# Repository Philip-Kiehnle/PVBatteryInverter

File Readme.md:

# PVBatteryInverter - Highly Efficient Photovoltaic and Battery Hybrid Inverter using GaN Semiconductors
This project was inspired by multiple drivers:
 * AC-connected battery systems have disadvantages in terms of charging efficiency ( PV -> DC/AC -> AC/DC -> Battery ) and cost/environmental impact, because of the additional inverter.  
 A multilevel battery converter is efficient but does not offer a DC port for PV and thus, increases installed converter power in the grid and grid operators have to calculate the worst case for grid utilization.
 * DC-connected battery systems do not guarantee a better efficiency by default. E.g. in case of a large inverter (~10 kW) operating under small loads during nighttime (30–150 Watt).
 * Commercial solutions often require an additional power meter for the self-consumption power control. In my opinion, this is a complete waste of time, space, resources and energy:
   * The installation is complicated, and requires space in the meter cabinet.
   * The additional power meter requires extra power of 0.4–2 Watt.
   * The additional power meter has an offset from the official meter measurement, meaning it cannot be used for exact zero-import control.
   * The digital energy meters in Germany already offer an optical interface, which can be set to send the actual power every second  [More details below](#head_electricityMeter)
 * GaN instead of SiC or Si-IGBT offers improved efficiency.
 * No GaN-based inverter is out there at the moment (9.12.2023)
 * Second-life 6 kWh battery was available
 * GaN full-bridge cells were available from another project
 * New west oriented PV plant has some shaded areas, which are directly connected to microinverter. But 8 PV-modules are unshaded most of the time and require a string inverter. A Hybrid (PV+Battery) Inverter for the unshaded PV-modules and a microinverter for the shaded PV-modules looks like the optimal solution.

Let's build an efficient 2kW hybrid inverter, which solves all the problems shown above!

System Overview:

# Components

## PV Plant
```
8 x 405 W PV-modules in the string
STC:
Vmpp_module(25°C) = 36.48 V
Impp_module(25°C) = 11.10 A
Voc_module(25°C)  = 46.30 V

Temperature Coefficients of Voc = -0.28 %
Voc_module(-15°C)  = 51.49 V
Voc_string(-15°C)  = 411.9 V -> 650 V GaN semiconductors
```

## High-Voltage Battery
```
nunm_cells = 96
Vmin = 96 * 3.3 V = 316.8 V (grid feed-in is only possible when grid rms voltage is below 224 V or by using reactive power)
Vnom = 96 * 3.7 V = 355.2 V
Vmax = 96 * 4.2 V = 403.2 V
energy = 18 Ah * 355.2 V = 6.4 kWh
```

## Inverter Housing
An unused inverter housing was available, including passive components like boost inductors and an LCL-filter, which can be reused.

A control PCB and GaN Full-Bridge PCBs were added. This picture was taken during the development phase:

### PV input
Common-Mode-Choke (CMC) -> Capacitor: MKP 900V  12.5uF +-5% -> Inductor -> Diode for PV string protection during development -> GaN Half-Bridge

### LCL-Filter
Inverter side inductor: 1mH

### GaN Full-Bridge
```
GaN semiconductors:
Gan Systems GS66508B 650 V
Rds_on(25°C)  =  50 mOhm
Rds_on(112°C) = 100 mOhm

estimated loss:
I = 2000 W ÷ 230 V = 8.7 A
50 % conduction of low and high-side switch
Pcond(112°C) = 0.5*0.1 Ohm*(8.7 A)^2 = 3.8 W per switch

Switching loss (according to datasheet at Vds = 400 V, Ids = 15 A):
Eon=47.5 µJ
Eoff=8 µJ
Pswitch = 20 kHz * (47.5+8) µJ = 1.1 W
-> 4.9 W have to be dissipated for each transistor 

Thermal Model:
R_JC = 0.5 K/W (manufacturer)
R_PCB = 3.39 K/W
R_TIM = 0.28 K/W
R_HSA = 4.8 K/W
R= 8.97 K/W
Thermal interface material coefficient seems too optimistic -> use R=10K/W
With ambient 40°C and junction = 112°C each transistor can dissipate P=(112-40)/10=7.2W
This assumption has enough tolerance because:
  -operating junction temperature is 150°C and not 112°C
  -dissipated power will be lower than 7.2W

If the power rating is set to 2300 W, the loss will increase to:
Ploss = Pswitch + 0.5*0.1 Ohm*(10 A)^2 = 1.1 W + 5 W = 6.1 W
But the inverter's inductors had an original design power of 2 kW. On the other hand, the ripple is lower than in the original design, because of an increased switching frequency.
This increases the core loss but the central inductor of phase L2 can be assumed as a heat sink, because it is not used.

Start heatsink fan at 1200W (5.2A) assume 90mOhm:
Ploss = Pswitch + 0.5*0.09 Ohm*(5.2 A)^2 = 1.1 W + 1.2 W = 2.3 W
Minimum runtime is 30 sec, stop if power after timer runtime is lower than 1 kW. Restart timer if power > 1.2 kW during fan runtime.
```

### Control board [PVBatteryInverter_Mainboard](PVBatteryInverter_Mainboard)
An STM32G474 microcontroller is used to control the system.

#### Code Execution:

HRTIM 20 kHz controls Grid Full-Bridge
1. HRTIM period triggers ADC1
2. ADC1 DMA done calls ADC_ConvComplete with hadc1 instance
3. ADC2 for PV current is started (two ADCs simultaneously cause disturbance!)
4. AC control algorithm is executed and new dutycycle is set
5. 45 µs after ADC2 start, the 128 PV/DC current samples are acquired and ADC DMA calls ADC_ConvComplete with hadc2 instance
6. DC control algorithm is executed and new dutycycle is set. Exact timing not relevant for slow MPP-Tracker
7. wait for new ADC1 samples

## Energy Management System
Todo: opensource the git repo and add link

## Default Electricity Meter

The Iskra electricity meter offers a power resolution of 1 Watt and a temporal resolution of 1 second.  
Its permanent energy counting registers are written every 100 mWh.  
This equals to a power mismatch of 360 W for 1 second.  
So the controller has to avoid that, which is possible most of the time.  
In case of large load steps, like hobs switching with 2 kW, there will be a mismatch.  
But experiments have shown that for a cooking session of 30 minutes, a mismatch of about 12 Wh occurs.  
If this amount is equally spread over 24 hours, the mismatch in each hour is 0.5 W.
To beat that value, an additional energy meter must:
  * consume less than 0.5 W
  * offer better temporal resolution than 1 second
  * offer no offset compared to the main electricity meter, or use an offset in feed-in direction and thus always feeds a little bit of power into the grid
  * come at no cost

This demonstrates the whole extent of stupidity to install an additional energy meter, if a digital electricity meter is already installed!  
A detailed analysis is also carried out in the [PowerSensorEmulator
](https://github.com/Philip-Kiehnle/PowerSensorEmulator
) repository.

# Efficiency

## Power Consumption
Assuming 90 % efficiency of the 5 V power supply.

### Mode "Connected to AC Grid - Passive"
The gate signals are turned off whenever there is no exchange of AC power.

BMS: 6 W  
Smartphone: 1 W  
PV-Boost GaN Full-Bridge not switching: 5 V ⋅ 90 mA / 0.9 = 0.5 W  
Grid GaN Full-Bridge not switching: 5 V ⋅ 90 mA / 0.9 = 0.5 W  
Grid Relay: 0.4 W  
STM32_PVBatteryInverter PCB:  5 V ⋅ 50 mA / 0.9 = 0.28 W (todo: check)  
STM32_BatterySupervisor PCB:  5 V ⋅ 40 mA / 0.9 = 0.22 W (todo: check)  

**Total: 8.9 W**

### Mode "Idle"
BMS 12 V power supply is OFF, so the idle consumption is reduced to **2.9 W**.  
The BMS reactivation and the routine for closing contactors takes about 10 seconds.

### Mode "Connected to AC Grid - Active"
Todo: measure efficiency curve

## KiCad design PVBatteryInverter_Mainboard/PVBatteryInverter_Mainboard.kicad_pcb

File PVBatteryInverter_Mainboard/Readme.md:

# Aisler PCB made in Germany
minium amount: 3pcs  
area: 100mm*60mm = 60cm²  
```
Price Budget 2-Layer: 10€ + 3* 60*0.0525€/cm² = 19,45€ -> 23,15€
Price HD 2-Layer:     12€ + 3* 60*0.084€/cm²  = 27,12€ -> 32,27€
Price HD 4-Layer:     12€ + 3* 60*0.117€/cm²  = 33,06€ -> 39,34€
```

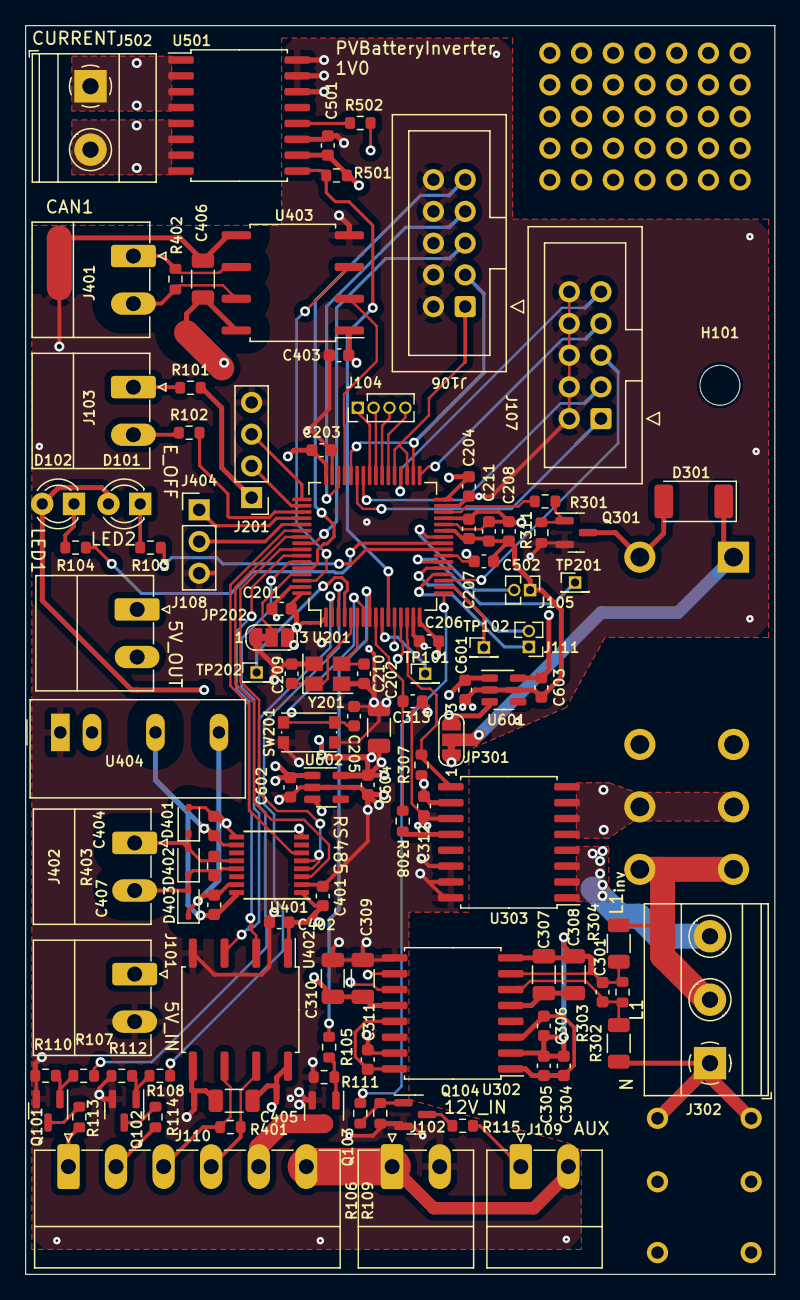
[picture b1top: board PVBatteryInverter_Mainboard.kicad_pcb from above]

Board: 4 copper layers, 60.0 x 100.0 mm, 116 parts (1 on the bottom side), 100 nets.

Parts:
C201, C203, C204, C205, C206, C211, C306, C311, C312, C401, C402, C403, C404, C407, C501: 100n; C_0603_1608Metric
C202: 4u7; C_1206_3216Metric
C207: 10n; C_0603_1608Metric
C208, C304: 1u; C_0603_1608Metric
C209, C210, C301: 10p; C_0603_1608Metric
C305: 1n; C_0603_1608Metric
C307, C405, C406: 100n; C_1206_3216Metric
C308, C309: 1n; C_1206_3216Metric
C310: 1µ; C_1206_3216Metric
C313, C502: 2n2; C_0603_1608Metric
C601, C602, C603, C604: 1µ; C_0603_1608Metric
D101, D102: LED; LED_D3.0mm
D301: US1D 200V 1A 50ns Silizium SMA; D_MELF
D401, D402, D403: D_TVS; D_SOD-323
H101: MountingHole; MountingHole_3.2mm_M3
J101: 5V_IN; PhoenixContact_MC_1,5_2-G-3.81_1x02_P3.81mm_Horizontal
J102: 12V_IN; PhoenixContact_MC_1,5_2-G-3.81_1x02_P3.81mm_Horizontal
J103: EMERGENY_OFF; PhoenixContact_MC_1,5_2-G-3.81_1x02_P3.81mm_Horizontal
J104: TIM; PinHeader_1x04_P1.27mm_Vertical
J105: ADC2_12; PinHeader_1x02_P1.27mm_Vertical
J106: FB_Boost; IDC-Header_2x05_P2.54mm_Vertical
J107: FB_Grid; IDC-Header_2x05_P2.54mm_Vertical
J108: 5V_OUT; PhoenixContact_MC_1,5_2-G-3.81_1x02_P3.81mm_Horizontal
J109: AUX_OpenDrain; PhoenixContact_MC_1,5_2-G-3.81_1x02_P3.81mm_Horizontal
J110: BMS; PhoenixContact_MC_1,5_6-G-3.81_1x06_P3.81mm_Horizontal
J111: ADC2_3-4; PinHeader_1x02_P1.27mm_Vertical
J201: SW_DBG; PinHeader_1x04_P2.54mm_Vertical
J302: 230V; TerminalBlock_Phoenix_MKDS-1,5-3-5.08_1x03_P5.08mm_Horizont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
J401: CAN1; PhoenixContact_MC_1,5_2-G-3.81_1x02_P3.81mm_Horizontal
J402: RS485; PhoenixContact_MC_1,5_2-G-3.81_1x02_P3.81mm_Horizontal
J404: UART; PinHeader_1x03_P2.54mm_Vertical
J502: Current sense; TerminalBlock_Phoenix_MKDS-1,5-2-5.08_1x02_P5.08mm_Horizont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
JP202: BOOT_MODE; SolderJumper-3_P1.3mm_Bridged12_RoundedPad1.0x1.5mm_NumberL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
JP301: SolderJumper_3_Bridged12; SolderJumper-3_P1.3mm_Bridged12_RoundedPad1.0x1.5mm_NumberL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
NT301, NT403, NT404: NetTie_2; NetTie-2_SMD_Pad0.5mm
NT401, NT402: NetTie_2; NetTie-2_SMD_Pad2.0mm
NT601: GNDA; NetTie-2_SMD_Pad0.5mm
Q101, Q102, Q104: BSS138; SOT-23
Q103, Q301: IRLML2502; SOT-23
R101, R102: 1k; R_0603_1608Metric
R103, R104, R308, R502: 220; R_0603_1608Metric
R105, R106, R107, R108, R113, R114, R115, R301: 100; R_0603_1608Metric
R109, R110, R111, R112, R311: 100k; R_0603_1608Metric
R302, R304: 470k; R_1206_3216Metric
R303: 2.70k; R_0603_1608Metric
R307, R501: 10k; R_0603_1608Metric
R401, R402, R403: 120; R_0603_1608Metric
RL301: JW2; Relay_DPDT_Panasonic_JW2
SW201: RESET; SW_Push_1P1T_NO_CK_KMR2
TP101: ADC1_IN8; PinHeader_1x01_P1.27mm_Vertical
TP102: TIM3_CH2; PinHeader_1x01_P1.27mm_Vertical
TP201: PC4; PinHeader_1x01_P1.27mm_Vertical
TP202: PC15; PinHeader_1x01_P1.27mm_Vertical
U201: STM32G474RETx; LQFP-64_10x10mm_P0.5mm
U302: AMC3330; SOIC-16W_7.5x10.3mm_P1.27mm
U303, U501: MCA1101-50-5; SOIC-16W_7.5x10.3mm_P1.27mm
U401: ISO1500; SSOP-16_3.9x4.9mm_P0.635mm
U402, U403: ISO1050DUB; SOP-8_6.62x9.15mm_P2.54mm
U404: TMR_1-0511; Converter_DCDC_TRACO_TMR-1-xxxx_Single_THT
U601, U602: TPS7A0333PDBVR; SOT-23-5
Y201: 12 MHz; Crystal_SMD_SeikoEpson_TSX3225-4Pin_3.2x2.5mm

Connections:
+3V3: C201.1, C202.1, C203.1, C204.1, C206.1, C309.1, C310.1, C401.1, C402.1, C403.1, C604.1, D101.2 (A), D102.2 (A), J201.1, JP202.3 (B), R101.2, U201.1 (VBAT), U201.16 (VDD), U201.32 (VDD), U201.48 (VDD), U201.64 (VDD), U302.12 (VDD), U401.1 (VCC1), U402.1 (VCC1), U403.1 (VCC1), U602.5 (OUT)
+5V: C312.1, C501.1, C601.1, C602.1, J101.1, J108.1, J108.2, JP301.3 (B), NT401.1, NT403.1, R307.2, R501.2, U303.10 (VCC), U404.2 (+VIN), U501.10 (VCC), U601.1 (IN), U601.3 (EN), U602.1 (IN), U602.3 (EN)
+12V: J102.1, J109.2, J110.6, JP301.1 (A)
/AC grid/AMC3330_OUTN: U201.13 (PA1), U302.10 (OUTN)
/AC grid/AMC3330_OUTP: U201.12 (PA0), U302.11 (OUTP)
/AC grid/Contactor_{Grid}: R301.1, U201.30 (PB10)
/AC grid/Igrid_{+}: C313.1, R308.2, U201.9 (PC1)
/AC grid/L1_{grid_sw}: RL301.3, RL301.6, U303.5 (IP-), U303.6 (IP-), U303.7 (IP-), U303.8 (IP-)
/AC grid/L1_{grid}: J302.2, R304.2, RL301.4, RL301.5
/AC grid/L1_{inverter}: J302.3, U303.1 (IP+), U303.2 (IP+), U303.3 (IP+), U303.4 (IP+)
/AC grid/N: J302.1, R302.1
/AC grid/nFAULT_{MCA1101}: R307.1, U201.14 (PA2), U303.9 (~FAULTB)
/BMS_GND: J110.5, Q103.3 (D)
/Communication/5V_CAN1: C406.1, NT401.2, U403.8 (VCC2)
/Communication/5V_CAN2: C405.1, NT403.2, U402.8 (VCC2)
/Communication/5V_RS485: C404.1, C407.1, U401.10 (VCC2), U401.16 (VCC2), U404.4 (+VOUT)
/Communication/CAN1_{RX}: U201.45 (PA11), U403.2 (RXD)
/Communication/CAN1_{TX}: U201.62 (PB9), U403.3 (TXD)
/Communication/CAN2_{RX}: U201.58 (PB5), U402.2 (RXD)
/Communication/CAN2_{TX}: U201.59 (PB6), U402.3 (TXD)
/Communication/GND_CAN1: C406.2, NT402.2, U403.5 (GND2)
/Communication/GND_CAN2: C405.2, NT404.2, U402.5 (GND2)
/Communication/GND_RS485: C404.2, C407.2, D401.2 (A2), D403.1 (A1), U401.9 (GND2), U401.15 (GND2), U404.6 (-VOUT)
/Communication/RS485_{EN}: U201.57 (PB4), U401.4 (~RE), U401.5 (DE)
/Communication/RS485_{RX}: U201.55 (PD2), U401.3 (R)
/Communication/RS485_{TX}: U201.54 (PC12), U401.6 (D)
/Communication/UART_{RX}: J404.2, U201.53 (PC11)
/Communication/UART_{TX}: J404.1, U201.52 (PC10)
/Cont_{Bat2DCboost}: J110.1, R113.2
/DCcurrent_sense/CS+: J502.1, U501.1 (IP+), U501.2 (IP+), U501.3 (IP+), U501.4 (IP+)
/DCcurrent_sense/CS-: J502.2, U501.5 (IP-), U501.6 (IP-), U501.7 (IP-), U501.8 (IP-)
/DCcurrent_sense/Ipv_{+}: C502.1, R502.2, U201.23 (PC5)
/DCcurrent_sense/nFAULT_{MCA1101}: R501.1, U201.11 (PC3), U501.9 (~FAULTB)
/Microcontroller/+3V3A_{MCU}: C207.1, C208.1, C211.1, C603.1, U201.28 (VREF+), U201.29 (VDDA), U601.5 (OUT)
/Microcontroller/ADC1_IN8: TP101.1, U201.10 (PC2)
/Microcontroller/ADC2_IN3: J111.1, U201.20 (PA6)
/Microcontroller/ADC2_IN4: J111.2, U201.21 (PA7)
/Microcontroller/ADC2_IN12: J105.2, U201.26 (PB2)
/Microcontroller/BOOT0: JP202.2 (C), U201.61 (PB8)
/Microcontroller/EmergencyOFF: R102.2, U201.51 (PA15)
/Microcontroller/FB_Boost_{EN}: J106.9, U201.60 (PB7)
/Microcontroller/FB_Boost_{OverTemp}: J106.7, U201.46 (PA12)
/Microcontroller/FB_Boost_{PWMA}: J106.3, U201.34 (PB12), U201.44 (PA10)
/Microcontroller/FB_Boost_{PWMB}: J106.1, U201.35 (PB13), U201.37 (PB15)
/Microcontroller/FB_Boost_{VdcData}: J106.5, U201.56 (PB3)
/Microcontroller/FB_Grid_{EN}: J107.9, U201.36 (PB14)
/Microcontroller/FB_Grid_{OverTemp}: J107.7, U201.33 (PB11)
/Microcontroller/FB_Grid_{PWMA}: J107.3, U201.42 (PA8)
/Microcontroller/FB_Grid_{PWMB}: J107.1, U201.43 (PA9)
/Microcontroller/FB_Grid_{VdcData}: J107.5, U201.19 (PA5)
/Microcontroller/HRTIM1CH_{E1}: J104.2, U201.40 (PC8)
/Microcontroller/HRTIM1CH_{E2}: J104.1, U201.41 (PC9)
/Microcontroller/HRTIM1CH_{F1}: J104.4, U201.38 (PC6)
/Microcontroller/HRTIM1CH_{F2}: J104.3, U201.39 (PC7)
/Microcontroller/LED1: R103.1, U201.24 (PB0)
/Microcontroller/LED2: R104.1, U201.25 (PB1)
/Microcontroller/NRST: C205.1, SW201.1 (A), U201.7 (PG10)
/Microcontroller/PF0: C209.2, U201.5 (PF0), Y201.1
/Microcontroller/PF1: C210.2, U201.6 (PF1), Y201.3
/Microcontroller/SWCLK: J201.2, U201.50 (PA14)
/Microcontroller/SWDIO: J201.3, U201.49 (PA13)
/Microcontroller/TIM3_CH2: TP102.1, U201.18 (PA4)
Aux_OpenDrain: R106.1, U201.17 (PA3)
BMS_Power: R105.1, U201.8 (PC0)
CAN2_{H}: J110.4, R401.1, U402.7 (CANH)
CAN2_{L}: J110.3, R401.2, U402.6 (CANL)
Contactor_{Bat2DCboost}: R107.1, U201.2 (PC13)
Contactor_{Bat2Inverter}: R108.1, U201.3 (PC14)
GND: C201.2, C202.2, C203.2, C204.2, C205.2, C206.2, C209.1, C210.1, C309.2, C310.2, C311.2, C312.2, C313.2, C401.2, C402.2, C403.2, C501.2, C601.2, C602.2, C604.2, J101.2, J102.2, J106.2, J106.4, J106.6, J106.8, J106.10, J107.2, J107.4, J107.6, J107.8, J107.10, J201.4, J404.3, JP202.1 (A), NT402.1, NT404.1, NT601.2, Q101.2 (S), Q102.2 (S), Q103.2 (S), Q104.2 (S), Q301.2 (S), R109.1, R110.1, R111.1, R112.1, R311.1, SW201.2 (B), U201.15 (VSS), U201.31 (VSS), U201.47 (VSS), U201.63 (VSS), U302.9 (GND), U302.15 (DCDC_GND), U303.11 (GND), U303.14 (GND2), U303.15 (GND), U303.16 (VOC), U401.2 (GND1), U401.8 (GND1), U402.4 (GND1), U403.4 (GND1), U404.1 (-VIN), U501.11 (GND), U501.14 (GND2), U501.15 (GND), U501.16 (VOC), U601.2 (GND), U602.2 (GND), Y201.2, Y201.4
GNDA: C207.2, C208.2, C211.2, C502.2, C603.2, J105.1, NT601.1, U201.27 (VSSA)
unnamed: D101.1 (K), R103.2
unnamed: D102.1 (K), R104.2
unnamed: D301.2 (A), Q301.3 (D), RL301.8
unnamed: D301.1 (K), JP301.2 (C), RL301.1
unnamed: D401.1 (A1), D402.2 (A2), J402.1, R403.1, U401.12 (A)
unnamed: D402.1 (A1), D403.2 (A2), J402.2, R403.2, U401.13 (B)
unnamed: J103.1, R101.1
unnamed: J103.2, R102.1
unnamed: J109.1, R115.2
unnamed: J110.2, R114.2
unnamed: J401.1, R402.1, U403.6 (CANL)
unnamed: J401.2, R402.2, U403.7 (CANH)
unnamed: Q101.3 (D), R113.1
unnamed: Q101.1 (G), R107.2, R110.2
unnamed: Q102.3 (D), R114.1
unnamed: Q102.1 (G), R108.2, R112.2
unnamed: Q103.1 (G), R105.2, R111.2
unnamed: Q104.3 (D), R115.1
unnamed: Q104.1 (G), R106.2, R109.2
unnamed: Q301.1 (G), R301.2, R311.2
unnamed: TP201.1, U201.22 (PC4)
unnamed: TP202.1, U201.4 (PC15)
unnamed: C304.2, C305.2, C306.1, C307.2, C308.2, NT301.2, U302.2 (DCDC_HGND), U302.8 (HGND)
unnamed: C311.1, U302.13 (LDO_OUT), U302.16 (DCDC_IN)
unnamed: C304.1, C305.1, C306.2, U302.1 (DCDC_OUT), U302.3 (HLDO_IN)
unnamed: C307.1, C308.1, U302.5 (HLDO_OUT)
unnamed: C301.2, NT301.1, R303.2, R304.1, U302.7 (INN)
unnamed: C301.1, R302.2, R303.1, U302.6 (INP)
unnamed: R308.1, U303.12 (Vout)
unnamed: R502.1, U501.12 (Vout)

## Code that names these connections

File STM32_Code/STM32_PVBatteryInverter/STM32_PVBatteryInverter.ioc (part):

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Mcu.Name=STM32G474R(B-C-E)Tx
Mcu.Package=LQFP64
Mcu.UserName=STM32G474RETx
PA0.Mode=IN1-Differential
PA0.Signal=ADC1_IN1
PA1.Mode=IN1-Differential
PA1.Signal=ADC1_IN2
PA10.Signal=S_TIM1_CH3
PA11.Signal=FDCAN1_RX
PA12.GPIOParameters=GPIO_PuPd,GPIO_ModeDefaultEXTI
PA12.GPIO_ModeDefaultEXTI=GPIO_MODE_IT_RISING
PA12.GPIO_PuPd=GPIO_PULLUP
PA12.Signal=GPXTI12
PA13.Mode=Serial_Wire
PA13.Signal=SYS_JTMS-SWDIO
PA14.Mode=Serial_Wire
PA14.Signal=SYS_JTCK-SWCLK
PA15.GPIOParameters=GPIO_PuPd
PA15.GPIO_PuPd=GPIO_PULLDOWN
PA15.Signal=GPIO_Input
PA2.GPIOParameters=GPIO_ModeDefaultEXTI
PA2.GPIO_ModeDefaultEXTI=GPIO_MODE_IT_FALLING
PA2.Signal=GPXTI2
PA3.Signal=GPIO_Output
PA4.Signal=S_TIM3_CH2
PA5.Signal=S_TIM2_ETR
PA6.Signal=ADC2_IN3
PA7.Mode=INP
PA7.Signal=COMP2_INP
PA8.Mode=Output_TA1TA2
PA8.Signal=HRTIM1_CHA1
PA9.Mode=Output_TA1TA2
PA9.Signal=HRTIM1_CHA2
PB0.Signal=GPIO_Output
PB1.Signal=GPIO_Output
PB10.Signal=GPIO_Output
PB11.GPIOParameters=GPIO_PuPd,GPIO_ModeDefaultEXTI
PB11.GPIO_ModeDefaultEXTI=GPIO_MODE_IT_RISING
PB11.GPIO_PuPd=GPIO_PULLUP
PB11.Signal=GPXTI11
PB13.Mode=PWM Generation1 CH1N
PB13.Signal=TIM1_CH1N
PB14.Signal=GPIO_Output
PB15.Signal=TIM1_CH3N
PB2.Signal=ADC2_IN12
PB3.Signal=S_TIM4_ETR
PB4.Mode=Hardware Flow Control (RS485)
PB4.Signal=UART5_DE
PB5.Mode=FDCAN_Activate
PB5.Signal=FDCAN2_RX
PB6.Mode=FDCAN_Activate
PB6.Signal=FDCAN2_TX
PB7.Signal=GPIO_Output
PB9.Signal=FDCAN1_TX
PC0.Signal=GPIO_Output
PC1.Mode=IN7-Single-Ended
PC1.Signal=ADC1_IN7
PC10.Mode=Asynchronous
PC10.Signal=USART3_TX
PC11.Mode=Asynchronous
PC11.Signal=USART3_RX
PC12.Mode=Asynchronous
PC12.Signal=UART5_TX
PC13.Signal=GPIO_Output
PC14-OSC32_IN.Signal=GPIO_Output
PC15-OSC32_OUT.Signal=GPIO_Output
PC3.GPIOParameters=GPIO_ModeDefaultEXTI
PC3.GPIO_ModeDefaultEXTI=GPIO_MODE_IT_FALLING
PC3.Signal=GPXTI3
PC4.Signal=GPIO_Output
PC5.Mode=IN11-Single-Ended
PC5.Signal=ADC2_IN11
PC6.Signal=HRTIM1_CHF1
PC7.Signal=HRTIM1_CHF2
PC8.Signal=HRTIM1_CHE1
PC9.Signal=HRTIM1_CHE2
PD2.Mode=Asynchronous
PD2.Signal=UART5_RX
PF0-OSC_IN.Mode=HSE-External-Oscillator
PF0-OSC_IN.Signal=RCC_OSC_IN
PF1-OSC_OUT.Mode=HSE-External-Oscillator
PF1-OSC_OUT.Signal=RCC_OSC_OUT
RCC.HSE_VALUE=12000000
RCC.SYSCLKFreq_VALUE=170000000
RCC.SYSCLKSource=RCC_SYSCLKSOURCE_PLLCLK
board=custom

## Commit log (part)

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2023-12-09 PCB production V1; pin planning complete
2023-12-26 fixed some PCB components and added notes in schematic for PCB V2
2023-12-26 tested CAN, PWM, UART, ADCs and all Sensors
2023-12-30 MPP Tracker tested with 19V supply 35W bulb as pre resistor; 32Ohm load resistor; 33kOhm Vdc sense
2024-01-05 tested AC control with 15V transformer, LCL filter and 4 Ohm series resistor; charging to 30Vdc successful
2024-01-07 implemented battery CAN bus commands
2024-01-19 MPP-Tracker in C++
2024-01-22 added watchdog; PV2AC with 10Watt at 48V
2024-01-22 without 5R6 AC precharge resistor; AC current 61mA offset; power consumption from DC and AC!
2024-01-26 PV boost auto switch to interleaved mode
2024-01-28 calib Vac and Vdc; implemented sml read -> tested in parallel with BMS and inverterdata output on same RS485 bus
2024-01-30 improved writing to monitor vars; grid voltage filter for matching amplitude; NO contactor or current feedforward
2024-01-30 monitor stream sync; MPPT too fast for grid control
2024-02-05 improved Vdc control speed; improved model, still mismatch: Pac=80W with 135W request
2024-02-07 fixed RC-lowpass freq
2024-02-17 inductor saturation LUT; dummy electr. meter
2024-03-16 PV battery charging and switch to PCC compensation tested
2024-03-17 improved battery_connected detection
2024-03-17 bootloader working; no autostart
2024-03-21 bootloader autostarts application if emergency button released at reset; RS485 update working
2024-03-21 battery update request always triggers send_inverterdata
2024-03-28 improved PV2AC mode; high PV input increases V_dc within seconds until EC_V_DC_SENSOR_FB_BOOST -> 4.0Aamp AC limit is not enough
2024-03-31 bootloader RS485 init after Jump, otherwise Comm in App broken; reworked hybrid states
2024-04-01 improved stability; optional print
2024-04-02 fixed mon_duty; fixed P_bat_const control; fixed AC turnoff during sunrise
2024-04-08 enabled global MPPT
2024-04-08 fixed gatedriver still disabled in PV2AC mode
2024-04-15 prevent short AC turnoff in the evening; improved battery handling and GMPPT
2024-04-16 status for enable_battery command
2024-04-23 added RS485 command interface
2024-05-02 fixed overvoltage error in transition from PV2AC to Hybrid mode
2024-05-03 added errorcodes for battery; fixed unaligned access in sml_parser
2024-05-13 reset microcontroller if battery switched off
2024-06-25 decreased PV start voltage; increased interval for RMS current fault
2024-10-10 charge Vcell to 3.50V instead of 3.56V added dynamic shift to direct voltage feedforward added grid voltage and freq error codes added external Pac control fixed power direction: grid to battery
2024-11-24 updated BMS struct (Kalman SoC and cycle counter)
2024-12-01 fixed battery_almost_full condition
2024-12-09 switched RS485 text parameter interface to Modbus; reset hybrid mode if main mode is changed
2024-12-14 reset Modbus after SML cycle (each second); update BMS lib
2024-12-16 shutdown of already discharged battery when PV power is low
2024-12-25 increased minimum battery cell voltage and prevent early battery shutdown to prevent BMS DEVICE_XREADY fault
2024-12-25 Battery Supervisor Board: CAN Bus RX test
2024-12-25 HV Vbat measurement circuit for PE connected microcontroller
2024-12-25 switched bootloader to internal oscillator
2024-12-30 STW_mBMS CAN read data and write balancing command
2025-01-02 fixed battery config; increased switching frequency to 40kHz, control still at 20kHz; tested voltage sensors and overcurrent Analog ADC watchdog
2025-01-07 5 minute charging test passed, using isolated AC-rectifier + 2x75W lightbulb as PV emulator; Test end with BMS unplug causing watchdog reset
2025-01-11 Battery_Supervisor: fixed voltage measurement circuit
2025-01-11 5 minute charging test passed using both PCBs; added shared code folder
2025-01-12 transmit battery current from Supervisor to Inverter
2025-01-13 Added GPIO interrupts for current sensor fault signals. Tested with Supervisor PCB and 60A AC pulse. Added GPIO interrupts for overtemperature. Tested with 1kOhm instead of NTC.
2025-01-13 Fixed overtemperature signal with 10nF. Added Kalman filter for SoC. Tested modbus registers for cell voltages. 15min 31W charging test passed.
2025-01-16 test with 320V DC and 33V AC RMS passed
2025-01-17 added 5V supply undervoltage detection to protect GaN from low gatevoltage. Tested trigger at ~4.65V.
2025-01-17 added nonlinear inductor model which was used in 48V system; remanent model is in rp-tfm repo
2025-01-19 new modbus regs: balancing state; v_pv reference
2025-01-19 31Vac 3.1Arms current test; 320Vdc
2025-01-26 230V AC grid with 30mA RCD and 2x1kW debug resistance: idle power ~3W, 15VA; disabled energy packet controller; avoid frequent contactor actions in case of grid voltage drop during contactor close; s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
2025-01-30 tested direct 230V AC grid with 30mA RCD; power meter: 2.6-5.2W, 80VA
2025-01-30 tested direct 230V AC grid with 10mA RCD
2025-01-30 added fan control
2025-01-31 improved UART monitoring
2025-02-01 ISR reordered to avoid noise of ADC2 disturbing ADC1; only one ADC should run at the same time; added second ISR debug pin; 8x oversampling for ADC1
2025-02-02 enabled and tested analog watchdog for AC current
2025-02-02 calib i_ac offset
2025-02-02 trigger ADC before CNT_MAX; checked ac duty calc duration max 5.1+18.4 = 23.5us < 25us
2025-02-03 fixed PI controller saturation behaviour; calib Vac offset with 325V sine; tuned PLL phase shift
2025-02-08 garage charging test with PV emulator 2x75W
2025-02-09 fixed sporadically read of 4 cell voltages as 0V
2025-02-09 fixed sporadically read of temperatures as 0; fixed battery current limit; increased AC power to 460W
2025-02-16 added battery PCB temperature; improved AC charging; adjusted battery temperature limits
2025-02-16 fixed external power immediate reset to 0; fixed PI-controller saturation
2025-02-17 improved AC charging; increased AC current; scaled p_ac; increased min cell voltage; decreased cell imbalance limit; use modbus SoC limits
2025-02-22 increased Vdc limit; increased Vcell max; set Kalman SoC estimation parameters in application
2025-02-23 BMS improvements; changed default PV boost stage, because stage 1 needs repair; turnoff AC if Vbat < Vgrid"
2025-02-24 prevent boost stage non sensed overcurrent due to high PV boost ratio or rapid change
2025-03-03 prevent bms power turnon without sufficient v_dc; BMS lib: improved CAN rx using multiple filters
2025-03-09 battery supervisor: improved CAN robustness; green LED shows contactor status
2025-03-10 reduced max battery temperature limit; error turns BMS 12V off; added p_ac controller; reduced limit for interleaved DCDC mode
2025-03-15 inline gate EN and contactor functions for faster response; added modbus commands
2025-03-15 added modbus p_bat_dischg_max
2025-03-16 increased AC current and error limit; increased min PV power; fixed BMS turnoff
2025-03-21 fixed PV low power cnt
2025-03-25 modbus reg for AC low power packet mode
2025-03-25 increased minimum cell voltage to avoid imbalance; increased AC power
2025-03-31 improved modbus write register (clamp before write); increased default minimum SoC
2025-04-12 increased AC power; battery i_discharge_max = 6A
2025-04-30 increased AC power to 1.5kW; increased BatterySupervisor pulse current limit from 10A to 15A; use advanced battery model for SoC estimation
2025-04-30 improved battery model: lower resistance; higher weight for coulomb counting
2025-05-13 increased AC power; added Modbus p_pcc_ref; added bat current limits for fault condition
2025-05-18 increased AC current error condition
2025-05-25 improved behaviour with empty battery; lowered max cell temp limit
2025-08-02 allow error reset after 30 seconds; improved PV2AC state switch; increased Pac and Iac_pulse_max; new MPPT: v_pv instead of dutycycle
2025-09-21 todo: cleanup readme
2025-10-08 increased Vpv,min; added SML submodule; increased controller speed for Ppcc controller
2025-11-22 fixed v_pv calculation; use PV2AC mode in the morning if p_pcc > 20W
2025-11-22 use PV2AC mode to start when V_pv > V_bat
2025-11-23 improved PV2AC and HYBRID mode change
2025-11-29 pv_power: calc RC lowpass; compensate DC link capacitor
2025-11-30 fixed mode change; pv_power: calc RC lowpass; compensate DC link capacitor
2025-12-15 added mode transition PV2AC to OFF in case of empty battery; improved PV2AC mode change; fixed voltage deviation error during battery turnoff
2026-02-28 reduced AC power to 1kW, which minimized AC current errors; started in december 2025, used until 28.2.2026
2026-03-02 added monitor variable ctrl_mode_AC; increased AC current
2026-03-04 modbus reg to disable use of battery; respect modbus SoC limit; limit MPPT power if required
2026-03-04 increased max Vdc
2026-05-17 interleaved MPPT
2026-05-18 added manual sensor calibration mode and PWM test mode
2026-05-21 use excess PV power for battery charging and ignore EMS charging power limit
2026-05-22 single boost converter stage
2026-06-04 added boost converter test
2026-06-05 improved dc_control
2026-06-13 preserve WatchdogRST flag in bootloader; check ISR runtime; check GaN reverse conduction (prevent system operation without active boost converter in case of high PV input current, which could damage 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
2026-06-29 increased max voltage and current
2026-06-30 fixed AC gatedriver pulse active because of PV power measurement noise; update Readme.md
